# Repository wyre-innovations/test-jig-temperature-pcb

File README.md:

# STM32G0-based Temperature Test Jig PCB

This repository contains the design and manufacturing files for a temperature test jig PCB based on the STM32G0 microcontroller, featuring a 16×2 LCD and 8 thermistor sensors.

### Project Structure

The project is organized into the following directories:

- `Design/`: Contains the KiCad design files.
    - `test-jig-temperature-pcb.kicad_pcb`: PCB layout file.
    - `test-jig-temperature-pcb.kicad_pro`: Project file.
    - `test-jig-temperature-pcb.kicad_sch`: Schematic file.
- `Docs/`: Documentation for the project.
    - `Schematic.pdf`: PDF version of the schematic.
- `Images/`: Images related to the project.
    - `Front.png`: Front view image.

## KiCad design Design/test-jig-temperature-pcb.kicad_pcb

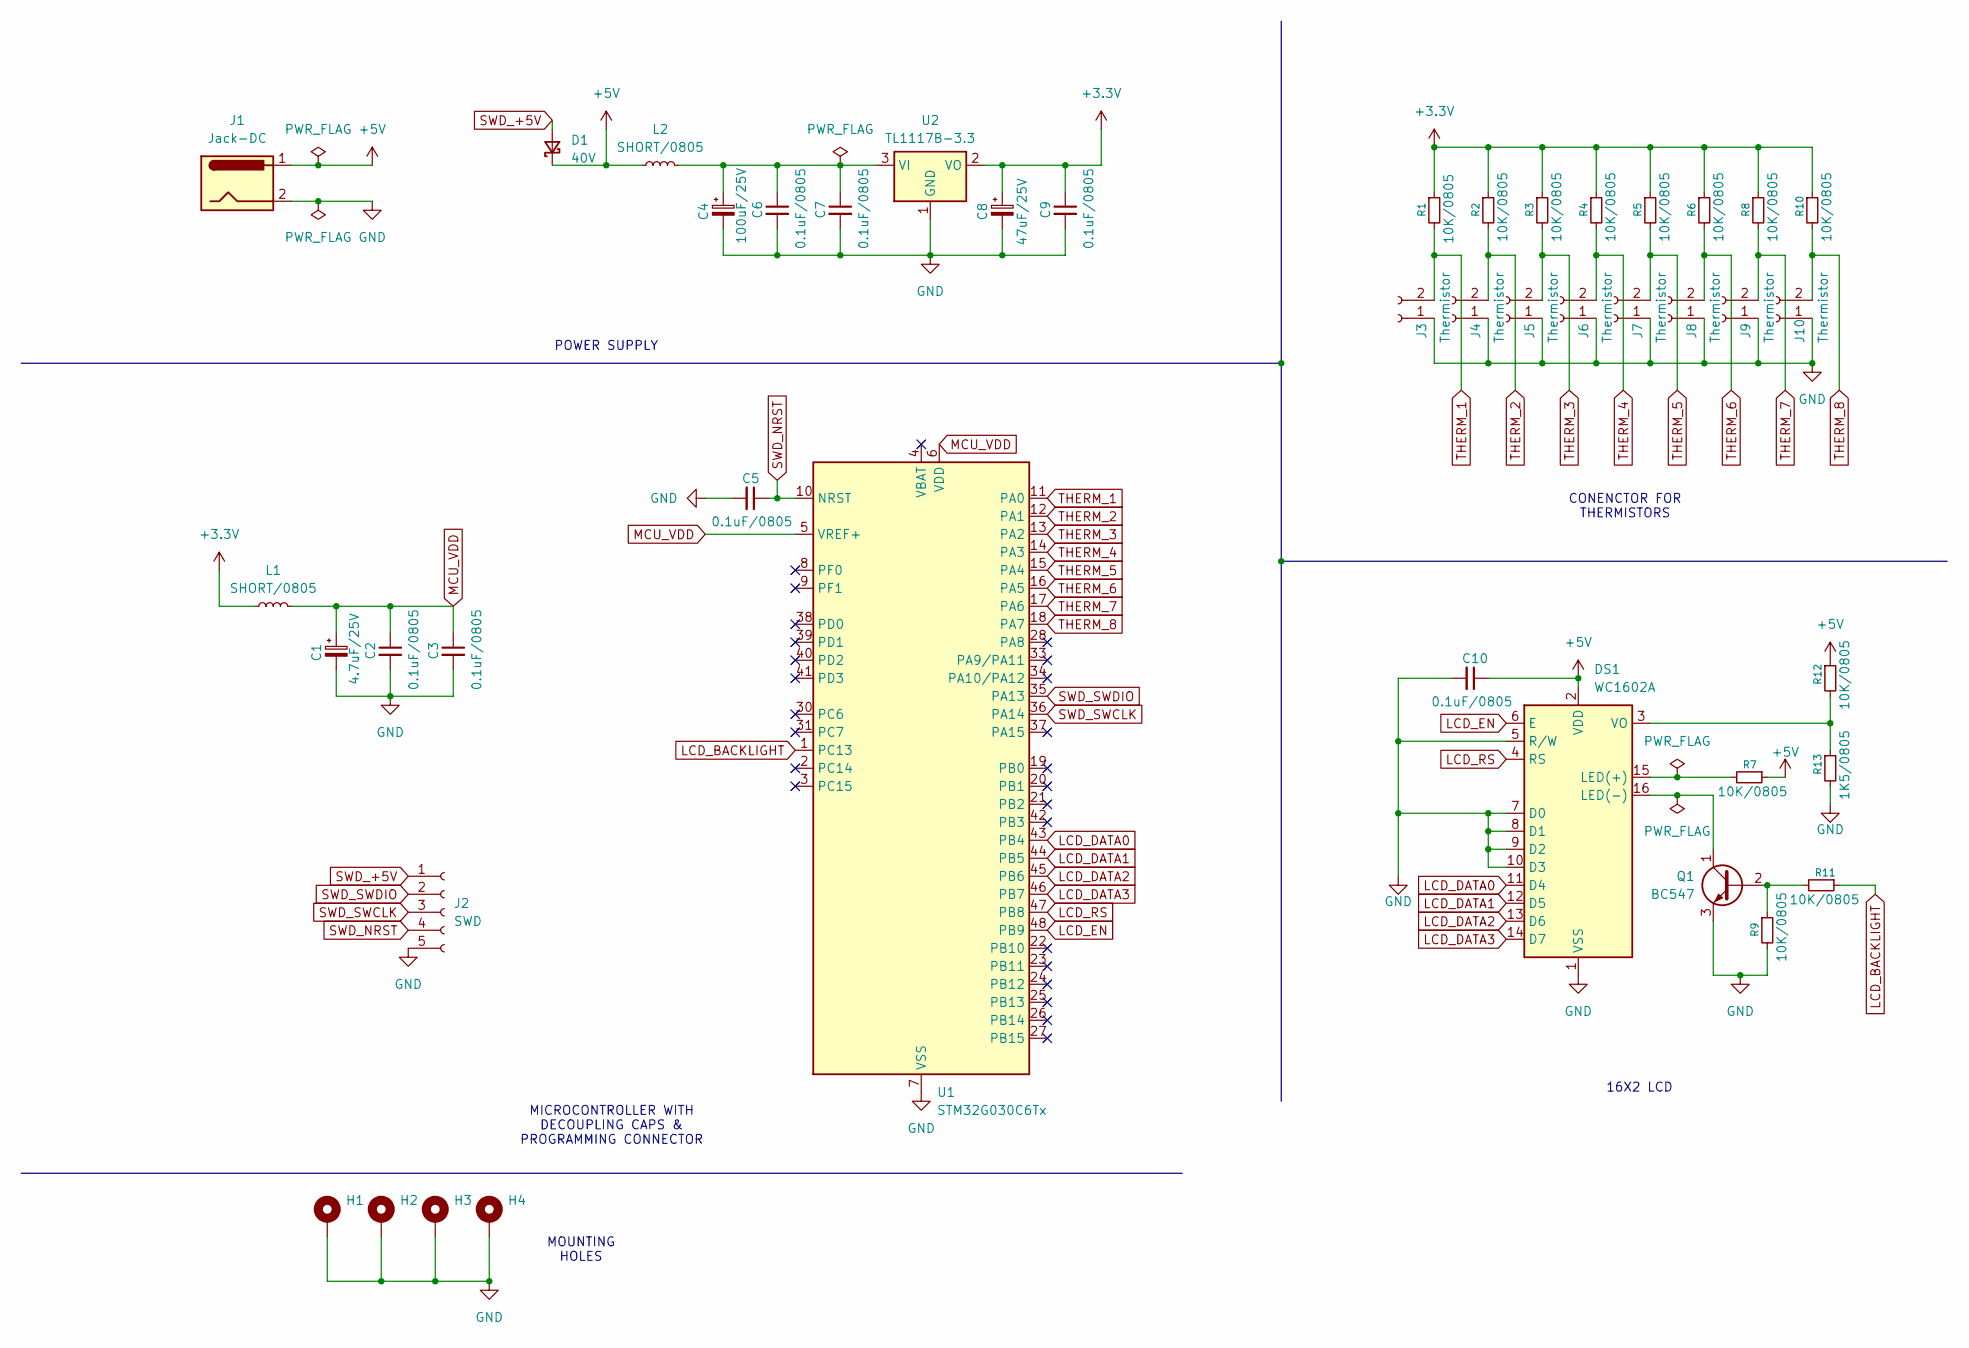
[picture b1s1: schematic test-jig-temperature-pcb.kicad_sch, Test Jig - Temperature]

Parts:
C1: 4.7uF/25V; CP_Radial_D5.0mm_P2.00mm
C2, C3, C5, C6, C7, C9, C10: 0.1uF/0805; C_0805_2012Metric_Pad1.18x1.45mm_HandSolder
C4: 100uF/25V; CP_Radial_D5.0mm_P2.00mm
C8: 47uF/25V; CP_Radial_D5.0mm_P2.00mm
D1: 40V; D_SMA_Handsoldering
DS1: WC1602A
H1, H2, H3, H4: MOUNTING HOLE; MountingHole_2.5mm_Pad
J1: Jack-DC; BarrelJack_Horizontal
J2: SWD; JST_XH_B5B-XH-A_1x05_P2.50mm_Vertical
J3, J4, J5, J6, J7, J8, J9, J10: Thermistor; JST_XH_B2B-XH-A_1x02_P2.50mm_Vertical
L1, L2: SHORT/0805; R_0805_2012Metric_Pad1.20x1.40mm_HandSolder
Q1: BC547; SOT-23
R1, R2, R3, R4, R5, R6, R7, R8, R9, R10, R11, R12: 10K/0805; R_0805_2012Metric_Pad1.20x1.40mm_HandSolder
R13: 1K5/0805; R_0805_2012Metric_Pad1.20x1.40mm_HandSolder
U1: STM32G030C6Tx; LQFP-48_7x7mm_P0.5mm
U2: TL1117B-3.3; SOT-223-3_TabPin2

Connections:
+3.3V: C8.1, C9.1, L1.1, R1.1, R2.1, R3.1, R4.1, R5.1, R6.1, R8.1, R10.1, U2.2 (VO)
+5V: C10.1, D1.1 (K), DS1.2 (VDD), J1.1, L2.1, R7.1, R12.1
GND: C1.2, C2.2, C3.2, C4.2, C5.2, C6.2, C7.2, C8.2, C9.2, C10.2, DS1.1 (VSS), DS1.5 (R/W), DS1.7 (D0), DS1.8 (D1), DS1.9 (D2), DS1.10 (D3), H1.MP, H2.MP, H3.MP, H4.MP, J1.2, J2.5, J3.1, J4.1, J5.1, J6.1, J7.1, J8.1, J9.1, J10.1, Q1.3 (E), R9.2, R13.2, U1.7 (VSS), U2.1 (GND)
LCD_BACKLIGHT: R11.1, U1.1 (PC13)
LCD_DATA0: DS1.11 (D4), U1.43 (PB4)
LCD_DATA1: DS1.12 (D5), U1.44 (PB5)
LCD_DATA2: DS1.13 (D6), U1.45 (PB6)
LCD_DATA3: DS1.14 (D7), U1.46 (PB7)
LCD_EN: DS1.6 (E), U1.48 (PB9)
LCD_RS: DS1.4 (RS), U1.47 (PB8)
MCU_VDD: C1.1, C2.1, C3.1, L1.2, U1.5 (VREF+), U1.6 (VDD)
unnamed: DS1.15 (LED(+)), R7.2
unnamed: DS1.16 (LED(-)), Q1.1 (C)
unnamed: DS1.3 (VO), R12.2, R13.1
unnamed: Q1.2 (B), R9.1, R11.2
unnamed: C4.1, C6.1, C7.1, L2.2, U2.3 (VI)
SWD_+5V: D1.2 (A), J2.1
SWD_NRST: C5.1, J2.4, U1.10 (NRST)
SWD_SWCLK: J2.3, U1.36 (PA14)
SWD_SWDIO: J2.2, U1.35 (PA13)
THERM_1: J3.2, R1.2, U1.11 (PA0)
THERM_2: J4.2, R2.2, U1.12 (PA1)
THERM_3: J5.2, R3.2, U1.13 (PA2)
THERM_4: J6.2, R4.2, U1.14 (PA3)
THERM_5: J7.2, R5.2, U1.15 (PA4)
THERM_6: J8.2, R6.2, U1.16 (PA5)
THERM_7: J9.2, R8.2, U1.17 (PA6)
THERM_8: J10.2, R10.2, U1.18 (PA7)

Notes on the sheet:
16X2 LCD
MICROCONTROLLER WITH DECOUPLING CAPS & PROGRAMMING CONNECTOR
CONENCTOR FOR THERMISTORS
MOUNTING HOLES
POWER SUPPLY

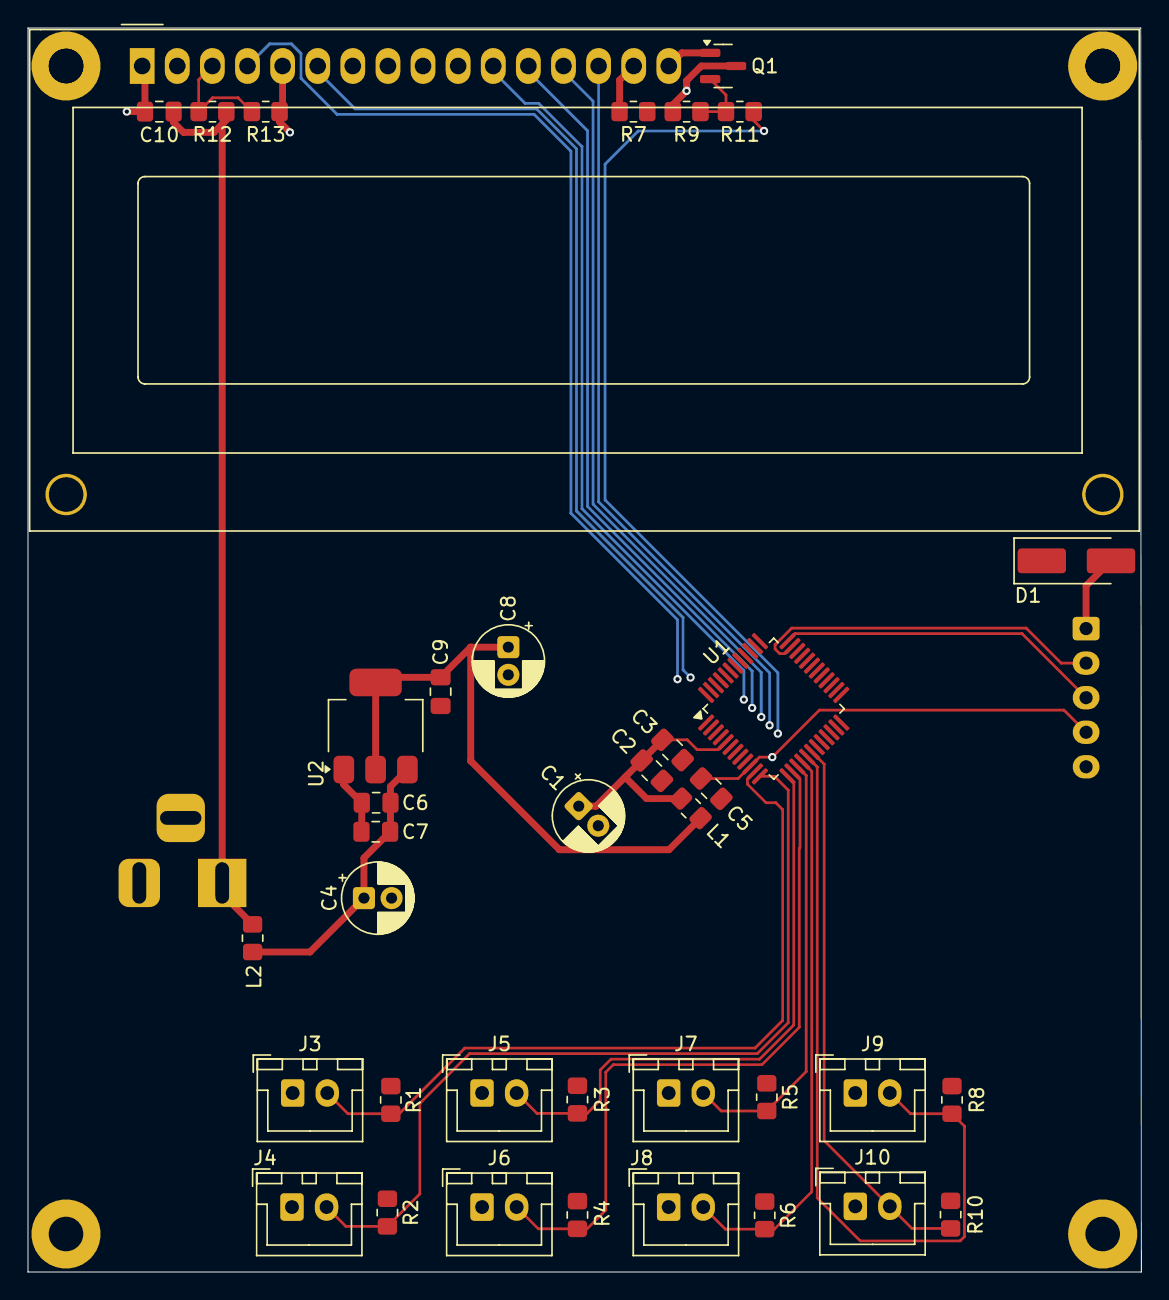
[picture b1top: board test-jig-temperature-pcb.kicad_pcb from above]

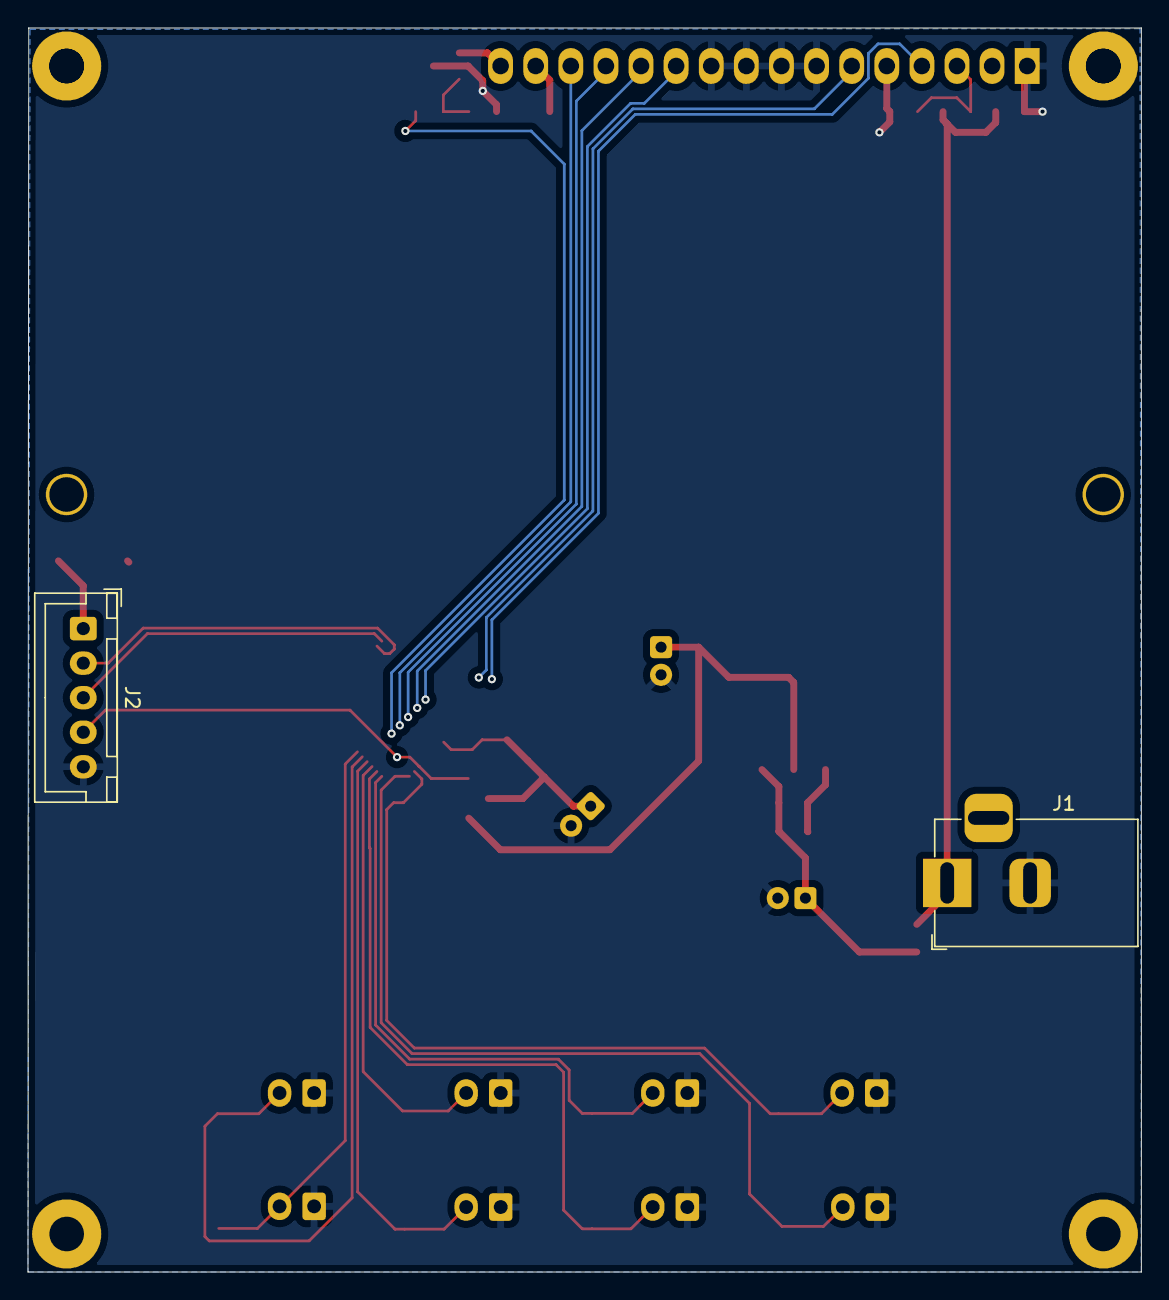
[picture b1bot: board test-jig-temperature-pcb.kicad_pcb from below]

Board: 2 copper layers, 80.5 x 90.0 mm, 44 parts (2 on the bottom side), 28 nets.

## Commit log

2025-10-01 Add KiCad design files
2025-10-01 Add schematic
2025-10-01 Fix ERC issues and re-annotate schematic
2025-10-04 Assign footprints to symbols
2025-10-20 Group components and route thermistor connector to MCU
2025-10-21 Route the 16x2 LCD to the microcontroller
2025-10-21 Reposition thermistor connectors and re-route connections
2025-10-22 Route components in power supply section and update README with current PCB image and project structure details
